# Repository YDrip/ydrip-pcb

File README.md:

# Open-Source Water Meter Hardware Design

## Description

This repository contains the open-source hardware design files for a water meter. The design was created using KiCad 6.

## Features

- High-precision water metering
- Low power consumption
- Compact and cost-effective design
- Compatible with standard water metering infrastructure
- Customizable digital logic

## Details

Panalization command

```bash
	kikit panelize \
	--layout 'grid; rows: 2; cols: 2; space: 2mm' \
	--tabs 'fixed; width: 8mm; vcount: 2; hcount: 1'\
	--cuts 'mousebites; drill: 0.5mm; spacing: 1mm; offset: 0.2mm; prolong: 0.5mm'\
	--framing 'frame; width: 5mm; space: 3mm;'\
	--copperfill solid\
	--post 'millradius: 1mm;' water_meter.kicad_pcb panel.kicad_pcb
```

## License

This project is licensed under the CERN Open Hardware Licence Version 2 - Weakly Reciprocal. Please see the `LICENSE.txt` file for more details.

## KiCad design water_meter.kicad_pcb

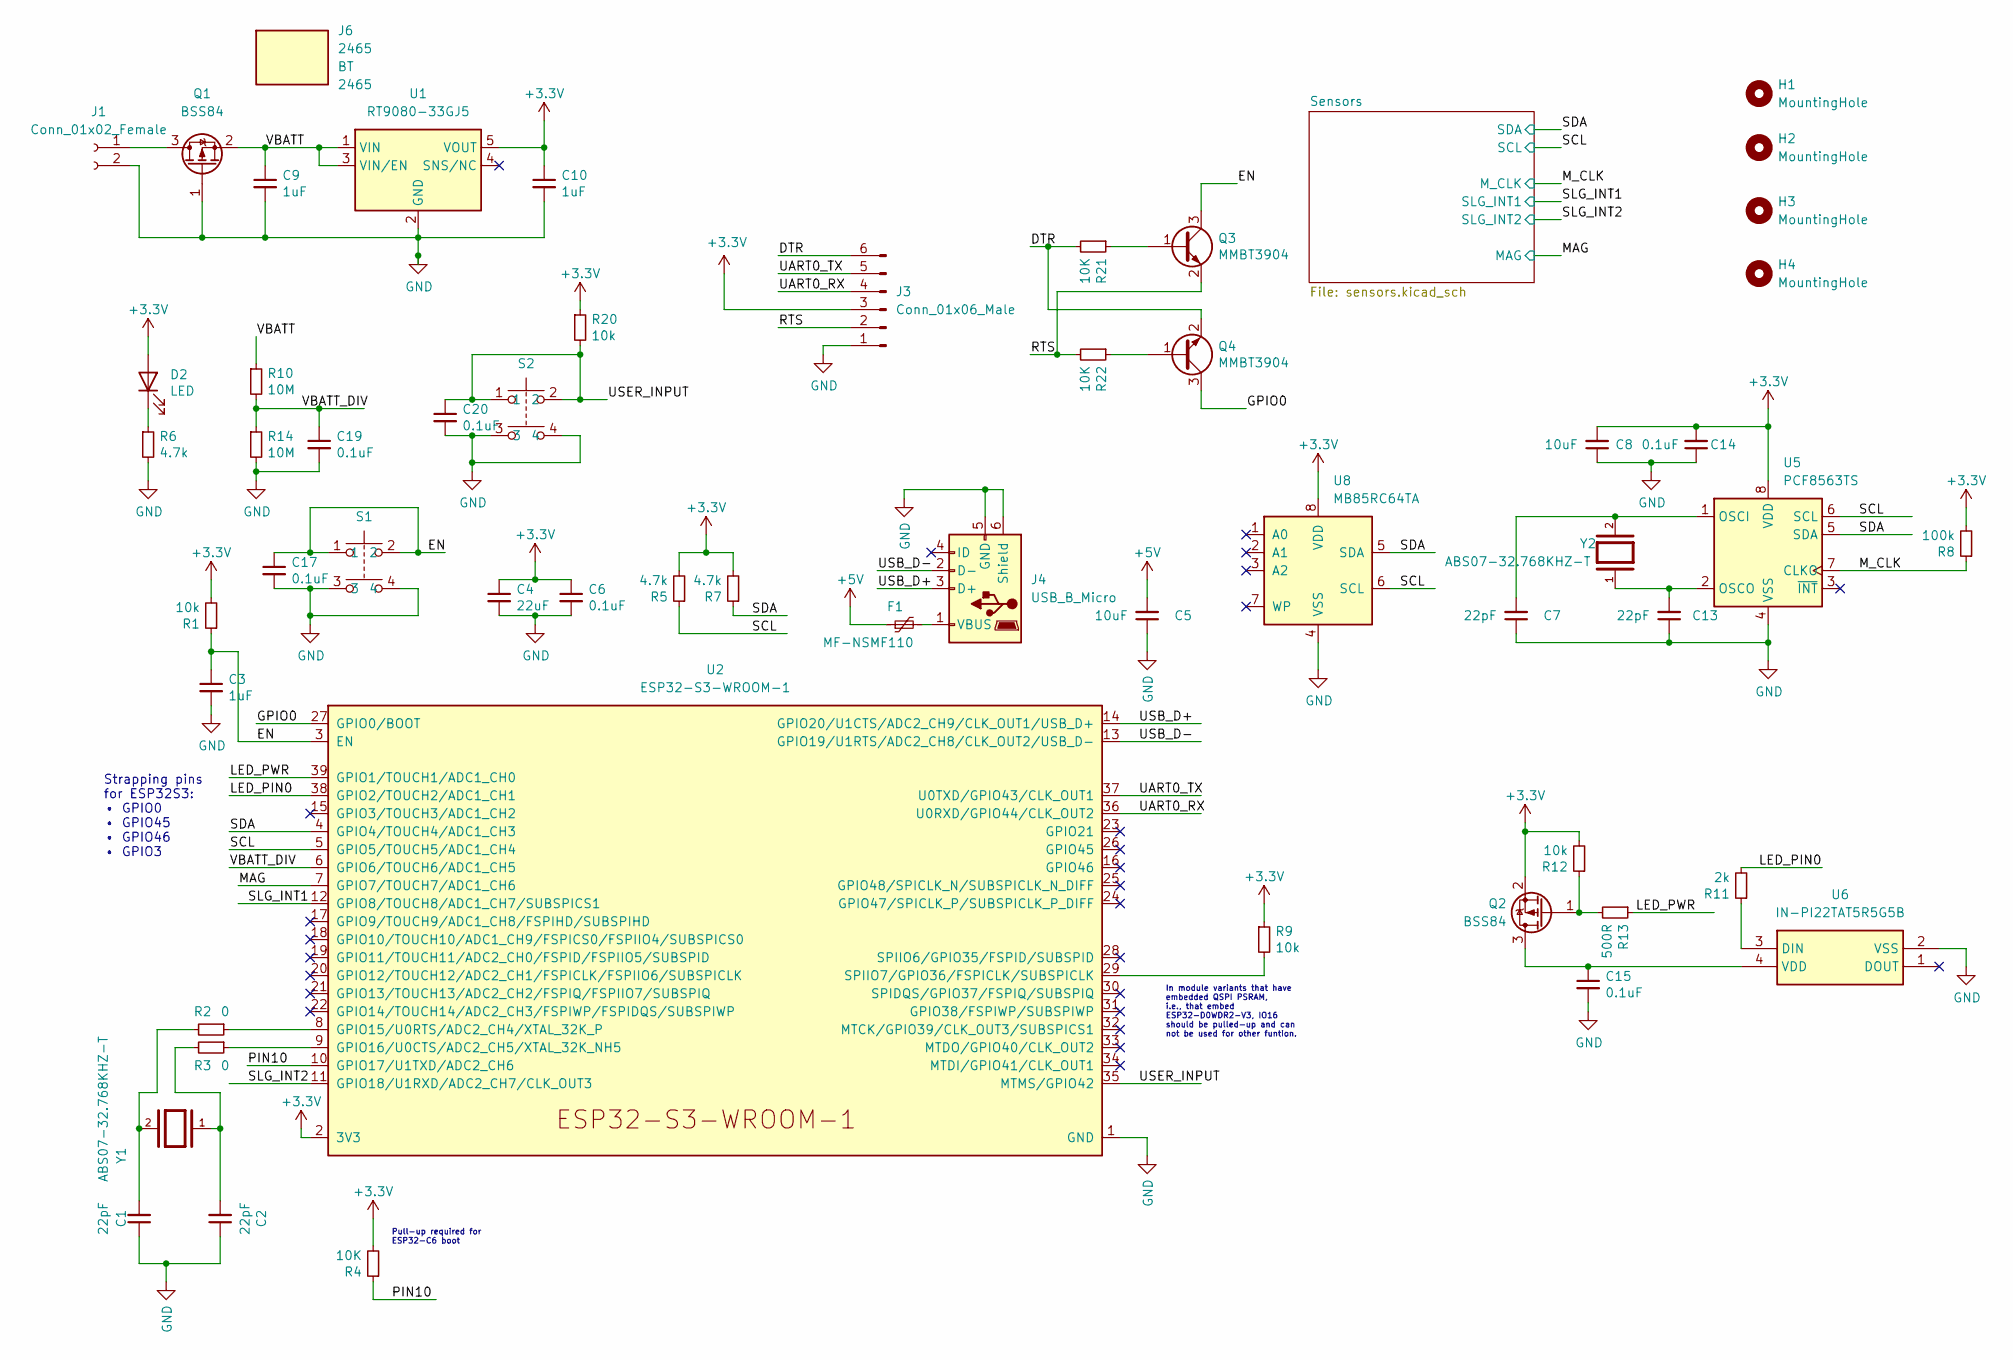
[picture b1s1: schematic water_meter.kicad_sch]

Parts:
C1, C2, C7, C13: 22pF; C_0805_2012Metric
C3, C9, C10: 1uF; C_0805_2012Metric
C4: 22uF; C_0805_2012Metric
C5, C8: 10uF; C_0805_2012Metric
C6, C14, C15, C17, C19, C20: 0.1uF; C_0805_2012Metric
D2: LED; LED_0805_2012Metric
F1: MF-NSMF110; Fuse_1206_3216Metric; Mouser Part Number 652-MF-NSMF110-2
H1, H2, H3, H4: MountingHole; MountingHole_3.2mm_M3
J1: Conn_01x02_Female; JST_PH_B2B-PH-SM4-TB_1x02-1MP_P2.00mm_Vertical
J3: Conn_01x06_Male; PinSocket_1x06_P2.54mm_Vertical
J4: USB_B_Micro; USB_Micro-B_Molex-105133-0001
J6: 2465; Manufacturer_Part_Number 2465; Mouser Part Number 534-2465
Q1, Q2: BSS84; SOT-23; Mouser Part Number 771-BSS84AK215
Q3, Q4: MMBT3904; SOT-23
R1, R9, R12, R20: 10k; R_0805_2012Metric
R2, R3: 0; R_0805_2012Metric
R4: 10K; R_0805_2012Metric
R5, R6, R7: 4.7k; R_0805_2012Metric
R8: 100k; R_0805_2012Metric
R10, R14: 10M; R_0805_2012Metric
R11: 2k; R_0805_2012Metric
R13: 500R; R_0805_2012Metric
R21, R22: 10K; R_0805_2012Metric_Pad1.20x1.40mm_HandSolder
S1, S2: PTS526_SK15_SMTR2_LFS; PTS526SK15SMTR2LFS; Manufacturer_Part_Number PTS526 SK15 SMTR2 LFS; Mouser Part Number 611-PTS526SK15SMR2L
U1: RT9080-33GJ5; SOT-23-5_HandSoldering; Digikey Part Number 1028-1509-1-ND
U2: ESP32-S3-WROOM-1; ESP32-S3-WROOM-1U; Mouser Part Number 356-ESP32S3WROM1UN16
U5: PCF8563TS; MSOP-8_3x3mm_P0.65mm; Mouser Part Number 771-PCF8563TS/5118
U6: IN-PI22TAT5R5G5B; INPI22TAT5R5G5B; Manufacturer_Part_Number IN-PI22TAT5R5G5B; Mouser Part Number 743-IN-PI22TAT5R5G5B
U8: MB85RC64TA; SOIC-8_3.9x4.9mm_P1.27mm; Mouser Part Number 249-85C64TAPNFGBDR1
Y1, Y2: ABS07-32.768KHZ-T; XTAL_ABS07-32.768KHZ-T; PARTREV 08.19.15; Mouser Part Number 815-ABS07-32.768KHZT

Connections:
+3V3: C4.1, C6.1, C8.2, C10.1, C14.2, D2.2 (A), J3.3, Q2.2 (S), R1.2, R4.2, R5.2, R7.2, R8.2, R9.1, R12.2, R20.1, U1.5 (VOUT), U2.2 (3V3), U5.8 (VDD), U8.8 (VDD); also elsewhere on the board
+5V: C5.2, F1.1
/DTR: J3.6, Q4.2 (E), R21.2
/EN: C3.1, C17.1, Q3.3 (C), R1.1, S1.1, S1.2, U2.3 (EN)
/GPIO0: Q4.3 (C), U2.27 (GPIO0/BOOT)
/LED_PIN0: R11.2, U2.38 (GPIO2/TOUCH2/ADC1_CH1)
/LED_PWR: R13.1, U2.39 (GPIO1/TOUCH1/ADC1_CH0)
/MAG: U2.7 (GPIO7/TOUCH7/ADC1_CH6); also elsewhere on the board
/M_CLK: R8.1, U5.7 (CLKO); also elsewhere on the board
/PIN10: R4.1, U2.10 (GPIO17/U1TXD/ADC2_CH6)
/RTS: J3.2, Q3.2 (E), R22.2
/SCL: R5.1, U2.5 (GPIO5/TOUCH5/ADC1_CH4), U5.6 (SCL), U8.6 (SCL); also elsewhere on the board
/SDA: R7.1, U2.4 (GPIO4/TOUCH4/ADC1_CH3), U5.5 (SDA), U8.5 (SDA); also elsewhere on the board
/SLG_INT1: U2.12 (GPIO8/TOUCH8/ADC1_CH7/SUBSPICS1); also elsewhere on the board
/SLG_INT2: U2.11 (GPIO18/U1RXD/ADC2_CH7/CLK_OUT3); also elsewhere on the board
/UART0_RX: J3.4, U2.36 (U0RXD/GPIO44/CLK_OUT2)
/UART0_TX: J3.5, U2.37 (U0TXD/GPIO43/CLK_OUT1)
/USB_D+: J4.3 (D+), U2.14 (GPIO20/U1CTS/ADC2_CH9/CLK_OUT1/USB_D+)
/USB_D-: J4.2 (D-), U2.13 (GPIO19/U1RTS/ADC2_CH8/CLK_OUT2/USB_D-)
/USER_INPUT: C20.1, R20.2, S2.1, S2.2, U2.35 (MTMS/GPIO42)
/VBATT: C9.1, Q1.2 (S), R10.1, U1.1 (VIN), U1.3 (VIN/EN)
/VBATT_DIV: C19.1, R10.2, R14.1, U2.6 (GPIO6/TOUCH6/ADC1_CH5)
GND: C1.1, C2.1, C3.2, C4.2, C5.1, C6.2, C7.1, C8.1, C9.2, C10.2, C13.1, C14.1, C15.2, C17.2, C19.2, C20.2, J1.2, J3.1, J4.5 (GND), J4.6 (Shield), Q1.1 (G), R6.2, R14.2, S1.3, S1.4, S2.3, S2.4, U1.2 (GND), U2.1 (GND), U2.40 (GND), U2.41 (GND), U5.4 (VSS), U6.2 (VSS), U8.4 (VSS); also elsewhere on the board
unnamed: C1.2, R2.2, Y1.2
unnamed: C2.2, R3.2, Y1.1
unnamed: C7.2, U5.1 (OSCI), Y2.2
unnamed: C13.2, U5.2 (OSCO), Y2.1
unnamed: C15.1, Q2.3 (D), U6.4 (VDD)
unnamed: D2.1 (K), R6.1
unnamed: F1.2, J4.1 (VBUS)
unnamed: J1.1, Q1.3 (D)
unnamed: Q2.1 (G), R12.1, R13.2
unnamed: Q3.1 (B), R21.1
unnamed: Q4.1 (B), R22.1
unnamed: R2.1, U2.8 (GPIO15/U0RTS/ADC2_CH4/XTAL_32K_P)
unnamed: R3.1, U2.9 (GPIO16/U0CTS/ADC2_CH5/XTAL_32K_NH5)
unnamed: R9.2, U2.29 (SPIIO7/GPIO36/FSPICLK/SUBSPICLK)
unnamed: R11.1, U6.3 (DIN)

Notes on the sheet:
In module variants that have embedded QSPI PSRAM, i.e., that embed ESP32-D0WDR2-V3, IO16 should be pulled-up and can not be used for other funtion.
Pull-up required for ESP32-C6 boot
Strapping pins for ESP32S3: • GPIO0 • GPIO45 • GPIO46 • GPIO3

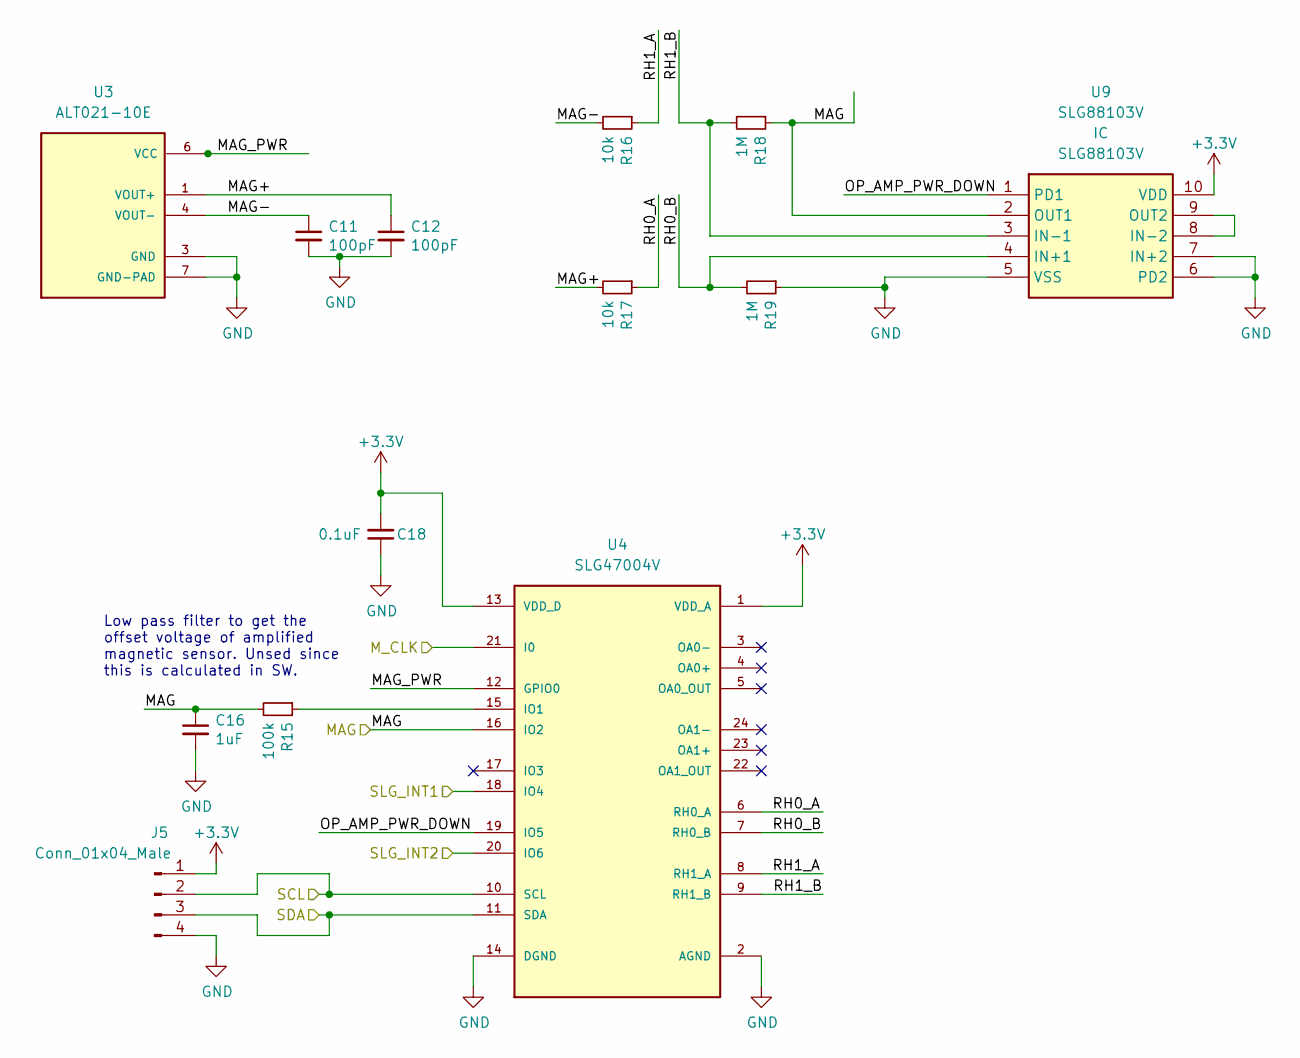
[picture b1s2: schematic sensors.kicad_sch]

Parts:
C11, C12: 100pF; C_0805_2012Metric
C16: 1uF; C_0805_2012Metric
C18: 0.1uF; C_0805_2012Metric
J5: Conn_01x04_Male; PinHeader_1x04_P2.54mm_Vertical
R15: 100k; R_0805_2012Metric
R16, R17: 10k; R_0805_2012Metric
R18, R19: 1M; R_0805_2012Metric
U3: ALT021-10E; SON65P250X250X80-7N; PARTREV November 2019
U4: SLG47004V; STQFN-24-3.0X3.0-A
U9: SLG88103V; Manufacturer_Part_Number SLG88103V

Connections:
+3V3: C18.2, J5.1, U4.1 (VDD_A), U4.13 (VDD_D), U9.10 (VDD); also elsewhere on the board
/MAG: C16.1, R15.2, R18.1, U4.16 (IO2), U9.2 (OUT1); also elsewhere on the board
/M_CLK: U4.21 (I0); also elsewhere on the board
/SCL: J5.2, U4.10 (SCL); also elsewhere on the board
/SDA: J5.3, U4.11 (SDA); also elsewhere on the board
/SLG_INT1: U4.18 (IO4); also elsewhere on the board
/SLG_INT2: U4.20 (IO6); also elsewhere on the board
/Sensors/MAG+: C12.1, R17.2, U3.1 (VOUT+)
/Sensors/MAG-: C11.1, R16.2, U3.4 (VOUT-)
/Sensors/MAG_PWR: U3.6 (VCC), U4.12 (GPIO0)
/Sensors/OP_AMP_PWR_DOWN: U4.19 (IO5), U9.1 (PD1)
/Sensors/RH0_A: R17.1, U4.6 (RH0_A)
/Sensors/RH0_B: R19.2, U4.7 (RH0_B), U9.4 (IN+1)
/Sensors/RH1_A: R16.1, U4.8 (RH1_A)
/Sensors/RH1_B: R18.2, U4.9 (RH1_B), U9.3 (IN-1)
GND: C11.2, C12.2, C16.2, C18.1, J5.4, R19.1, U3.3 (GND), U3.7 (GND-PAD), U4.2 (AGND), U4.14 (DGND), U9.5 (VSS), U9.6 (PD2), U9.7 (IN+2); also elsewhere on the board
unnamed: R15.1, U4.15 (IO1)
unnamed: U9.8 (IN-2), U9.9 (OUT2)

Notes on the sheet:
Low pass filter to get the offset voltage of amplified magnetic sensor. Unsed since this is calculated in SW.

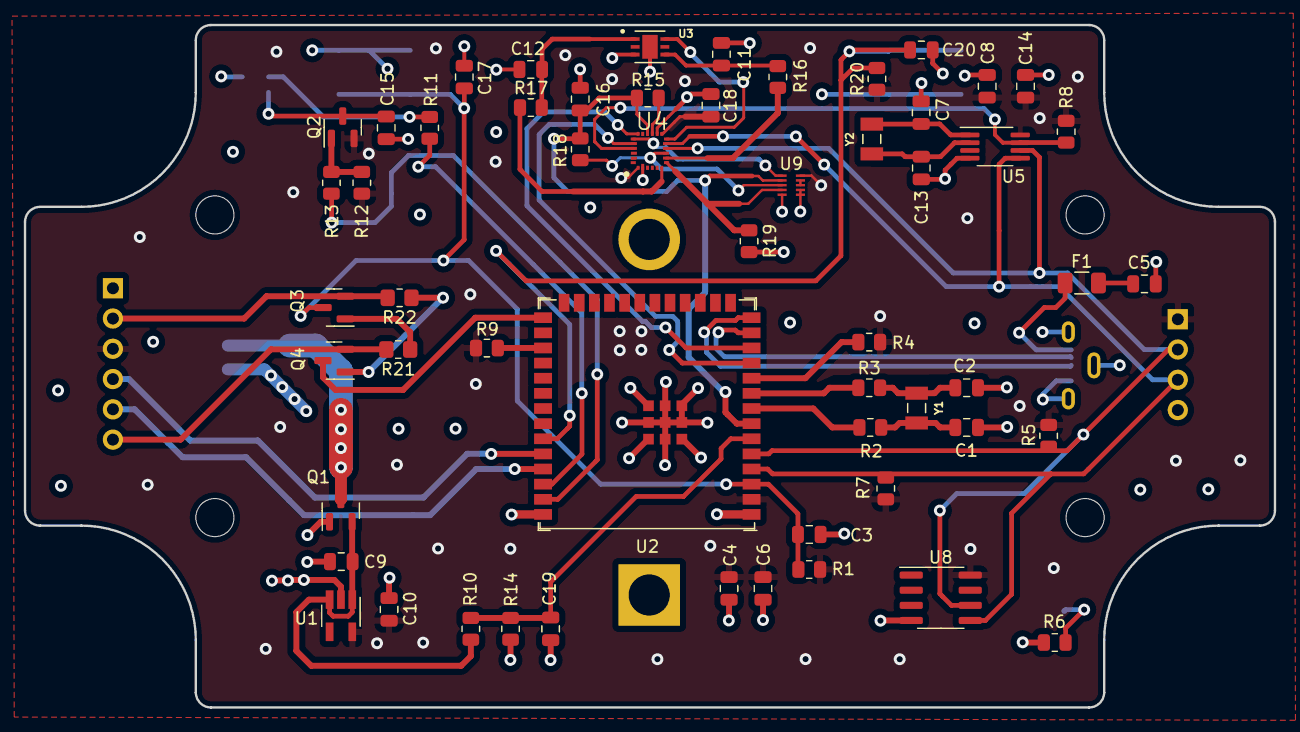
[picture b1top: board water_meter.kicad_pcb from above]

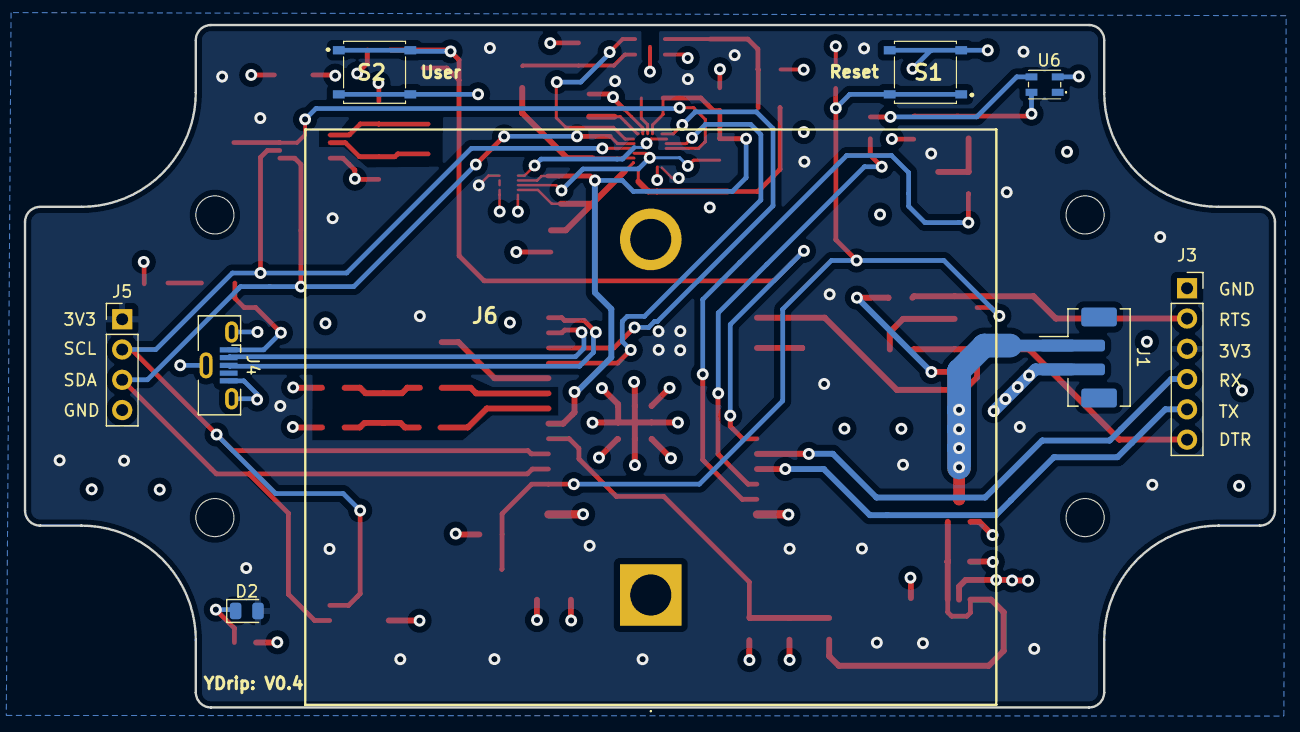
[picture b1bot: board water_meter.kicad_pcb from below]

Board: 4 copper layers, 104.9 x 57.3 mm, 69 parts (9 on the bottom side), 48 nets.

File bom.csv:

Source:,/home/nabil/Projects/water_meter/hardware/water_meter/water_meter.kicad_sch,,,,,
Date:,Tue 11 Apr 2023 01:28:04 PM EDT,,,,,
Tool:,Eeschema 6.0.11-2627ca5db0~126~ubuntu20.04.1,,,,,
Generator:,/usr/share/kicad/plugins/bom_csv_grouped_by_value.py,,,,,
Component Count:,52,,,,,
,,,,,,
,,,,,,
Collated Components:,,,,,,
,,,,,,
Item,Qty,Reference(s),Value,Footprint,Digikey Part Number,Mouser Part Number
1,4,"C1, C2, C7, C13",22pF,Capacitor_SMD:C_0805_2012Metric,,
2,3,"C3, C9, C10",1uF,Capacitor_SMD:C_0805_2012Metric,,
3,1,C4,22uF,Capacitor_SMD:C_0805_2012Metric,,
4,2,"C5, C8",10uF,Capacitor_SMD:C_0805_2012Metric,,
5,4,"C6, C14, C15, C16",0.1uF,Capacitor_SMD:C_0805_2012Metric,,
6,2,"C11, C12",100pF,Capacitor_SMD:C_0805_2012Metric,,
7,0,D2,LED,LED_SMD:LED_0805_2012Metric,,
8,0,F1,MF-NSMF110,Fuse:Fuse_1206_3216Metric,,652-MF-NSMF110-2
10,1,J1,2464,Nabil:2464,,534-2464
11,1,J3,Conn_01x06_Male,Connector_PinSocket_2.54mm:PinSocket_1x06_P2.54mm_Vertical,,
12,0,J4,USB_Micro-10118193-0001LF,Nabil:FCI_10118193-0001LF,,649-10118193-0001LF
13,1,J5,Conn_01x02_Male,Jumper:SolderJumper-2_P1.3mm_Bridged_Pad1.0x1.5mm,,
14,1,J8,Conn_01x02_Male,Connector_PinSocket_2.54mm:PinSocket_1x02_P2.54mm_Vertical,,
15,2,"Q1, Q2",BSS84,Package_TO_SOT_SMD:SOT-23,,771-BSS84AK215
16,2,"R1, R9",10k,Resistor_SMD:R_0805_2012Metric,,
17,2,"R2, R3",0,Resistor_SMD:R_0805_2012Metric,,
18,1,R4,10K,Resistor_SMD:R_0805_2012Metric,,
19,2,"R5, R7",4.7k,Resistor_SMD:R_0805_2012Metric,,
20,1,R6,5.1K,Resistor_SMD:R_0805_2012Metric,,
21,2,"R8, R10",100k,Resistor_SMD:R_0805_2012Metric,,
22,3,"R11, R12, R13",500R,Resistor_SMD:R_0805_2012Metric,,
24,1,U2,ESP32-S3-WROOM-1,Espressif:ESP32-S3-WROOM-1U,,356-ESP32S3WROM1UN16
26,1,U4,SLG46826G,Nabil:SOP65P640X120-20N,,724-SLG46826G
27,1,U5,PCF8563TS,Package_SO:MSOP-8_3x3mm_P0.65mm,,771-PCF8563TS/5118
28,1,U6,IN-PI22TAT5R5G5B,Nabil:INPI22TAT5R5G5B,,743-IN-PI22TAT5R5G5B
29,1,U7,10413_lens,Nabil:10414_Lens,,962-10413 
30,1,U8,MB85RC64TA,Package_SO:SOIC-8_3.9x4.9mm_P1.27mm,,249-85C64TAPNFGBDR1
31,2,"Y1, Y2",ABS07-32.768KHZ-T,Nabil:XTAL_ABS07-32.768KHZ-T,,815-ABS07-32.768KHZT
,,,,,,
,1,,SMA Antenna CAB.721,,,960-CAB721 
,,, Pulse Electronics Antenna W1030,,,673-W1030

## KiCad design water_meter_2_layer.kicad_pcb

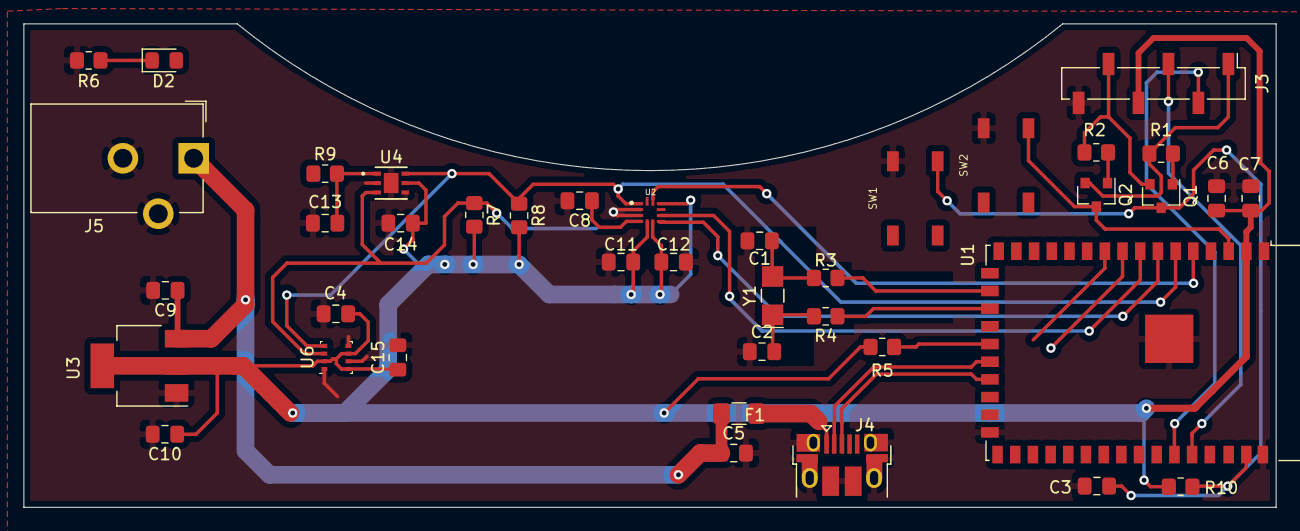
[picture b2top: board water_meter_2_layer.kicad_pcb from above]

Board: 2 copper layers, 106.2 x 41.0 mm, 40 parts (0 on the bottom side), 26 nets.

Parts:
C1, C2, C6: 22uF; C_0805_2012Metric_Pad1.18x1.45mm_HandSolder
C3, C9, C12, C13, C14: 1uF; C_0805_2012Metric_Pad1.18x1.45mm_HandSolder
C4, C8, C11, C15: 100nF; C_0805_2012Metric_Pad1.18x1.45mm_HandSolder
C5: 10uF/25V(20%); C_0805_2012Metric_Pad1.18x1.45mm_HandSolder
C7: 0.1uF; C_0805_2012Metric_Pad1.18x1.45mm_HandSolder
C10: 1uF(X5R); C_0805_2012Metric_Pad1.18x1.45mm_HandSolder
D2: LED; LED_0805_2012Metric_Pad1.15x1.40mm_HandSolder
F1: MF-NSMF110; Fuse_1206_3216Metric_Pad1.42x1.75mm_HandSolder
J3: Conn_01x06; PinSocket_1x06_P2.54mm_Vertical_SMD_Pin1Left
J4: USB_B_Micro; USB_Micro-B_Amphenol_10103594-0001LF_Horizontal
J5: Barrel_Jack_Switch; BarrelJack_CUI_PJ-102AH_Horizontal
Q1, Q2: MMBT3904; SOT-23
R1, R2: 10K(1%); R_0805_2012Metric_Pad1.20x1.40mm_HandSolder
R3, R4: 0; R_0805_2012Metric_Pad1.20x1.40mm_HandSolder
R5: 10K; R_0805_2012Metric_Pad1.20x1.40mm_HandSolder
R6: 5.1K; R_0805_2012Metric_Pad1.20x1.40mm_HandSolder
R7, R8: 4.7k; R_0805_2012Metric_Pad1.20x1.40mm_HandSolder
R9: 4.7; R_0805_2012Metric_Pad1.20x1.40mm_HandSolder
R10: 10k(1%); R_0805_2012Metric_Pad1.20x1.40mm_HandSolder
SW1, SW2: TL3342F160QG_TR
U1: ESP32-S2-WROVER
U2: LIS3MDLTR
U3: TLV1117LV33DCYR; SOT-223-3_TabPin2
U4: SGP30-2.5K
U6: BME280; Bosch_LGA-8_2.5x2.5mm_P0.65mm_ClockwisePinNumbering
Y1: 32.768kHz (ESR < 70 kΩ); Crystal_SMD_G8-2Pin_3.2x1.5mm_HandSoldering

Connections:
+3V3: C4.1, C6.1, C7.1, C10.1, C11.1, C12.1, C14.1, C15.1, D2.2, J3.4, R5.1, R7.2, R8.2, R9.1, R10.2, U1.2, U2.5, U2.6, U2.10, U3.2, U4.5, U6.2, U6.6, U6.8
+5V: C5.1, C9.1, F1.1, J5.1, U3.3
DTR: J3.1, Q2.2, R1.2
EN: C3.1, Q1.3, R10.1, SW1.2, U1.41
GND: C1.1, C2.1, C3.2, C4.2, C5.2, C6.2, C7.2, C8.2, C9.2, C10.2, C11.2, C12.2, C13.2, C14.2, C15.2, J3.6, J4.5, J4.6, J5.2, J5.3, R6.2, SW1.4, SW2.4, U1.1, U1.26, U1.42, U1.43, U2.2, U2.3, U2.9, U2.12, U3.1, U4.2, U4.4, U4.7, U6.1, U6.5, U6.7
I2C_CLK: R8.1, U1.6, U2.1, U4.6, U6.4
I2C_DATA: R7.1, U1.5, U2.11, U4.3, U6.3
IO00: Q2.3, SW2.2, U1.3
IO15: R3.1, U1.18
IO16: R4.1, U1.19
IO18: R5.2, U1.21
MAG_DRDY: U1.8, U2.8
MAG_INT: U1.7, U2.7
unnamed: C1.2, R3.2, Y1.2
unnamed: C2.2, R4.2, Y1.1
unnamed: C8.1, U2.4
unnamed: C13.1, R9.2, U4.1
unnamed: D2.1, R6.1
unnamed: F1.2, J4.1
unnamed: Q1.1, R1.1
unnamed: Q2.1, R2.1
RTS: J3.5, Q1.2, R2.2
UART_RX: J3.3, U1.38
UART_TX: J3.2, U1.37
USB_D+: J4.3, U1.23
USB_D-: J4.2, U1.22

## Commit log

2024-09-11 Prototype V0.4 - New board layout for new enclosure - Added user button - Using opamp power down pin to save power
2024-11-26 Minor bom changes for HW version 0.4 & added missing schematic

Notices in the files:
parts and their libraries:
Copyright 2016 Accelerated Designs. All rights reserved.
